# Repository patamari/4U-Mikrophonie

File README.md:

# 4U-Mikrophonie
4U adaptation of Mikrophonie for LW format

Original design by Tom Whitwell and Émilie Gillet

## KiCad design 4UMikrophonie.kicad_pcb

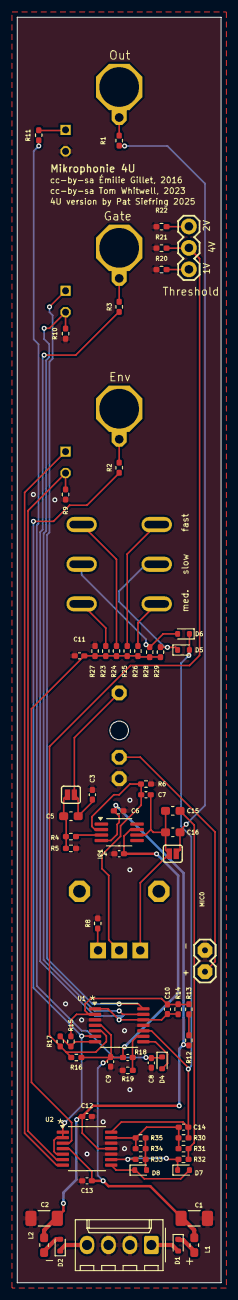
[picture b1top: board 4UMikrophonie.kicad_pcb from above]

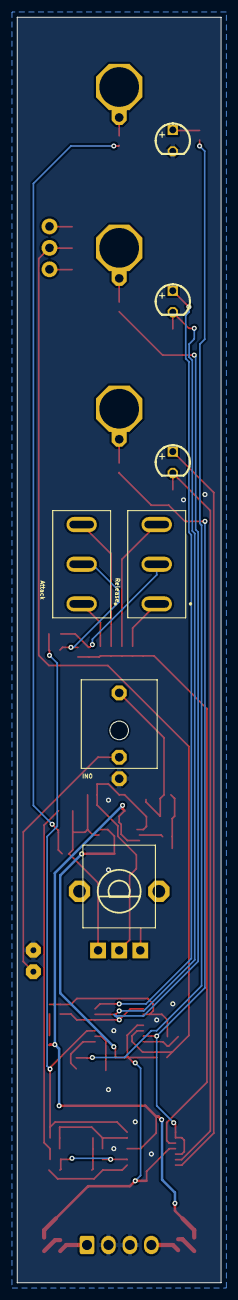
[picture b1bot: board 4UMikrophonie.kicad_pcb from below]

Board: 2 copper layers, 24.1 x 149.9 mm, 73 parts (7 on the bottom side), 42 nets.

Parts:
Attack: PanelMountSwitch4.7mm
C1, C2: 22u; C_1206_3216Metric_Pad1.33x1.80mm_HandSolder
C3, C10: 68p; C_0402_1005Metric_Pad0.74x0.62mm_HandSolder
C4, C6, C9, C12, C13: 100n; C_0402_1005Metric_Pad0.74x0.62mm_HandSolder
C5, C15, C16: 4.7u; C_0603_1608Metric_Pad1.08x0.95mm_HandSolder
C7: 22p; C_0402_1005Metric_Pad0.74x0.62mm_HandSolder
C8, C11: 1u; C_0402_1005Metric_Pad0.74x0.62mm_HandSolder
C14: 1.0n; C_0402_1005Metric_Pad0.74x0.62mm_HandSolder
D1, D2: PMEG2010AEB; D_SOD-523
D4, D5, D6, D7, D8: 1N4148; D_SOD-523
IC1: OPA1641; MSOP-8_3x3mm_P0.65mm
IN0: PJ301_THONKICONN6; WQP_PJ_301M6
JP2: 1X03
JP5, JP6: JUMPER-SMT_2_NO_SILK; SMT-JUMPER_2_NO_SILK_528
L1, L2: L_0603_1608Metric_Pad1.05x0.95mm_HandSolder
LED1: WP710A10SEC/J3; LED3MM
LED2_ENV0: AOL-3MWY4; LED3MM
LED3_GATE0: WP710A10SEC/J4; LED3MM
MIC0: 1X02_TINY
R1, R2, R3, R8: 510; R_0402_1005Metric_Pad0.72x0.64mm_HandSolder
R4, R6, R24: 10k; R_0402_1005Metric_Pad0.72x0.64mm_HandSolder
R5, R27: 1.0M; R_0402_1005Metric_Pad0.72x0.64mm_HandSolder
R7: 100kB; ALPS_POT_VERTICAL_PS
R9, R10, R11: LED; R_0402_1005Metric_Pad0.72x0.64mm_HandSolder
R12, R19, R20, R21, R23, R29, R33, R34, R35: 100k; R_0402_1005Metric_Pad0.72x0.64mm_HandSolder
R13, R14, R15, R16, R17, R30, R31, R32: 200k; R_0402_1005Metric_Pad0.72x0.64mm_HandSolder
R18: 20k; C_0402_1005Metric_Pad0.74x0.62mm_HandSolder
R22, R26: 20k; R_0402_1005Metric_Pad0.72x0.64mm_HandSolder
R25: 2.7k; R_0402_1005Metric_Pad0.72x0.64mm_HandSolder
R28: 430k; R_0402_1005Metric_Pad0.72x0.64mm_HandSolder
Release: PanelMountSwitch4.7mm
U1, U2: LM324; TSSOP-14_4.4x5mm_P0.65mm

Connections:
AMP_OUT: C7.2, C15.1, C16.1, IC1.6, JP6.1, R7.P$3
AMP_OUT_AC: C15.2, R31.1, R32.1
CLIP: D4.2, U1.8
ENVELOPE: R2.1, U1.6, U2.1, U2.2, U2.5
FULL_WAVE_RECT: C14.2, D5.2, D6.1, R30.2, U1.10, U2.14
GATE: C10.2, R3.1, R14.2, U1.1, U1.12
GND: C1.2, C2.1, C3.2, C4.2, C6.1, C8.2, C9.2, C11.2, C12.1, C13.2, IN0.P1, LED1.K, MIC0.1, R5.1, R6.2, R8.2, R9.2, R10.1, R19.1, R20.2, R21.2, R22.2, R27.1, U1.3, U1.11, U2.10, U2.12
unnamed: IC1.3, R4.1
unnamed: C3.1, C5.1, IN0.P3, JP5.1
unnamed: D7.2, D8.1, U2.8
unnamed: IN0.P2, MIC0.2
unnamed: C10.1, R13.2, R14.1, R15.2, U1.2
unnamed: C7.1, IC1.2, R6.1, R7.P$2
unnamed: C5.2, JP5.2, R4.2, R5.2
unnamed: D7.1, R32.2, R33.1, U2.9
unnamed: D8.2, R33.2, R34.1, R35.1
unnamed: R7.P$1, R8.1
unnamed: C14.1, R30.1, R31.2, R34.2, R35.2, U2.13
unnamed: C16.2, JP6.2, R1.1
unnamed: LED2_ENV0.K, R9.1, U2.6
unnamed: Attack.2, D5.1, R29.1
unnamed: C11.1, R23.2, R24.2, R25.2, R26.2, R27.2, R28.2, R29.2, U2.3
unnamed: R24.1, Release.3
unnamed: D1.1, L1.2
unnamed: R23.1, Release.1
unnamed: D6.2, R28.1, Release.2
unnamed: Attack.3, R25.1
unnamed: Attack.1, R26.1
unnamed: R18.1, R19.2, U1.9
unnamed: C8.1, D4.1, R11.2
unnamed: LED2_ENV0.A, U2.7
unnamed: LED1.A, R11.1
unnamed: JP2.2, R16.2, R17.1, R21.1, U1.5
unnamed: JP2.1, R22.1
unnamed: JP2.3, R20.1
unnamed: LED3_GATE0.K, R10.2, U1.13
unnamed: LED3_GATE0.A, U1.14
unnamed: R12.1, R13.1
unnamed: D2.2, L2.2
VCC: C1.1, C4.1, C9.1, C13.1, IC1.7, L1.1, R16.1, R18.2, U1.4, U2.4
VEE: C2.2, C6.2, C12.2, IC1.4, L2.1, R12.2, U2.11
~GATE: R15.1, R17.2, U1.7

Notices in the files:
4UMikrophonie.kicad_pcb:
cc-by-sa Émilie Gillet, 2016
cc-by-sa Tom Whitwell, 2023
